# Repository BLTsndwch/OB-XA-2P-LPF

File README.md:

# OB-XA-2P-LPF

Re-creation OB-XA 2 pole low pass filter.

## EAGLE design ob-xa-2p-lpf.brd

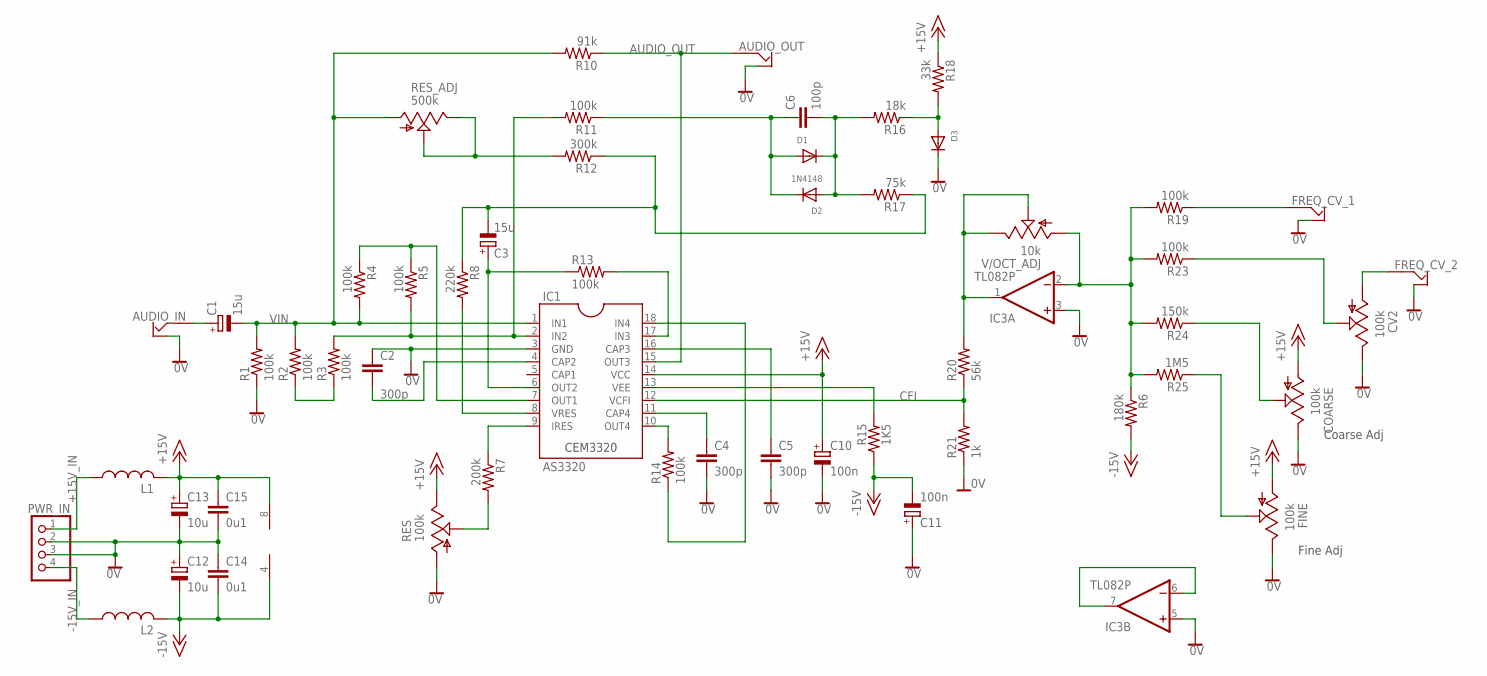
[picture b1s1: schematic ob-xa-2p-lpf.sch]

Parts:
AUDIO_IN: OFFBOARD2JACKALT
AUDIO_OUT: OFFBOARD2JACKALT
C1, C3: 15u; E1,8-4
C2, C4, C5: 300p; C050-025X075
C6: 100p; C050-025X075
C10, C11: 100n; E1,8-4
C12, C13: 10u; E1,8-4
C14, C15: 0u1; C050-025X075
COARSE: 100k; B64Y
CV2: 100k; B64Y
D1, D2, D3: 1N4148; DO-1N4148
FINE: 100k; B64Y
FREQ_CV_1, FREQ_CV_2: OFFBOARD2JACKALT
IC1: AS3320; DIL18
IC3: TL082P; DIL08
L1, L2: L-US0207/10; 0207/10
PWR_IN: PINHD-1X4; 1X04
R1, R2, R3, R4, R5, R11, R13, R14, R19, R23: 100k; 0207/10
R6: 180k; 0207/10
R7: 200k; 0207/10
R8: 220k; 0207/10
R10: 91k; 0207/10
R12: 300k; 0207/10
R15: 1K5; 0207/10
R16: 18k; 0207/10
R17: 75k; 0207/10
R18: 33k; 0207/10
R20: 56k; 0207/10
R21: 1k; 0207/10
R24: 150k; 0207/10
R25: 1M5; 0207/10
RES: 100k; B64Y
RES_ADJ: 500k; S63P
V/OCT_ADJ: 10k; S63P

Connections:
0V: AUDIO_IN.GND, AUDIO_OUT.GND, C2.1, C4.2, C5.2, C10.-, C11.+, C12.+, C13.-, C14.1, C15.2, COARSE.E, CV2.E, D3.C, FINE.E, FREQ_CV_1.GND, FREQ_CV_2.GND, IC1.3 (GND), IC3.3 (+IN), IC3.5 (+IN), PWR_IN.2, PWR_IN.3, R1.1, R21.1, RES.A
+15V: C10.+, C13.+, C15.1, COARSE.A, FINE.A, IC1.14 (VCC), IC3.8 (V+), L1.2, R18.1, RES.E
+15V_IN: L1.1, PWR_IN.1
-15V: C11.-, C12.-, C14.2, IC3.4 (V-), L2.2, R6.2, R15.1
-15V_IN: L2.1, PWR_IN.4
AUDIO_IN: AUDIO_IN.SIGNAL, C1.+
AUDIO_OUT: AUDIO_OUT.SIGNAL, IC1.15 (OUT3), R10.1
CFI: IC1.12 (VCFI), R20.1, R21.2
unnamed: R2.1, R3.1
unnamed: IC3.1 (OUT), R20.2, V/OCT_ADJ.E, V/OCT_ADJ.S
unnamed: IC1.2 (IN2), R3.2, R5.2, R11.2
unnamed: C2.2, IC1.4 (CAP2)
unnamed: IC1.7 (OUT1), R4.1, R5.1
unnamed: C3.+, IC1.6 (OUT2), R13.1
unnamed: C6.1, D1.A, D2.C, R11.1
unnamed: C6.2, D1.C, D2.A, R16.2, R17.2
unnamed: D3.A, R16.1, R18.2
unnamed: IC1.17 (IN3), R13.2
unnamed: IC1.10 (OUT4), R14.2
unnamed: IC1.18 (IN4), R14.1
unnamed: IC1.8 (VRES), R8.2
unnamed: C3.-, R8.1, R12.1, R17.1
unnamed: R12.2, RES_ADJ.E, RES_ADJ.S
unnamed: IC1.13 (VEE), R15.2
unnamed: IC1.9 (IRES), R7.1
unnamed: C4.1, IC1.11 (CAP4)
unnamed: R7.2, RES.S
unnamed: C5.1, IC1.16 (CAP3)
unnamed: IC3.6 (-IN), IC3.7 (OUT)
unnamed: IC3.2 (-IN), R6.1, R19.2, R23.2, R24.2, R25.2, V/OCT_ADJ.A
unnamed: FREQ_CV_1.SIGNAL, R19.1
unnamed: CV2.S, R23.1
unnamed: CV2.A, FREQ_CV_2.SIGNAL
unnamed: COARSE.S, R24.1
unnamed: FINE.S, R25.1
VIN: C1.-, IC1.1 (IN1), R1.2, R2.2, R4.2, R10.2, RES_ADJ.A

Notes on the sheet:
Fine Adj
Coarse Adj

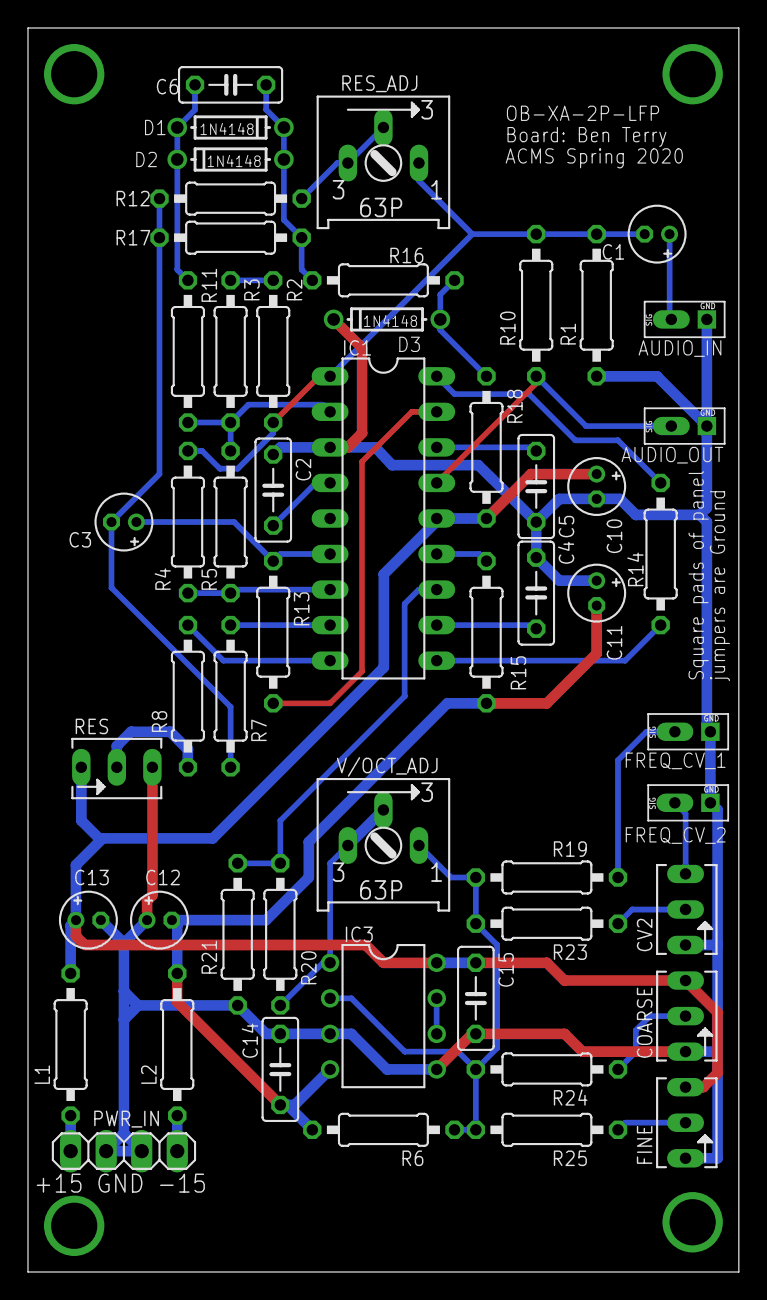
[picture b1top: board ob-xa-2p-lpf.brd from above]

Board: 2 copper layers, 50.8 x 88.9 mm, 53 parts (0 on the bottom side), 36 nets.

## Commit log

2020-04-09 init
2020-04-09 add gitignore
2020-04-10 make schematic
2020-04-10 init lib
2020-04-10 begin layout
2020-04-10 draft
2020-04-20 update project
2020-04-20 add cv imput
2020-04-20 add res ctrl
2020-04-20 drop -5V
2020-04-20 improve power
2020-04-20 layout CV
2020-04-23 layout everything
2020-04-23 more layout cleanup
2020-04-23 bit more layout cleanup
2020-04-23 route everything
2020-04-23 add mounting holes
2020-04-23 minor cleanup. Draft2 rev
2021-02-07 add images to readme
2021-02-07 fix path spec for images
    h*ck you, windows
